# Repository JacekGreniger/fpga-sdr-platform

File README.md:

FPGA based SDR platform

Codec: AD9963
FPGA: Spartan 6 LX9, clock 48MHz
Host interface: USB 2.0, CY7C68013A in FIFO mode, clock 24MHz

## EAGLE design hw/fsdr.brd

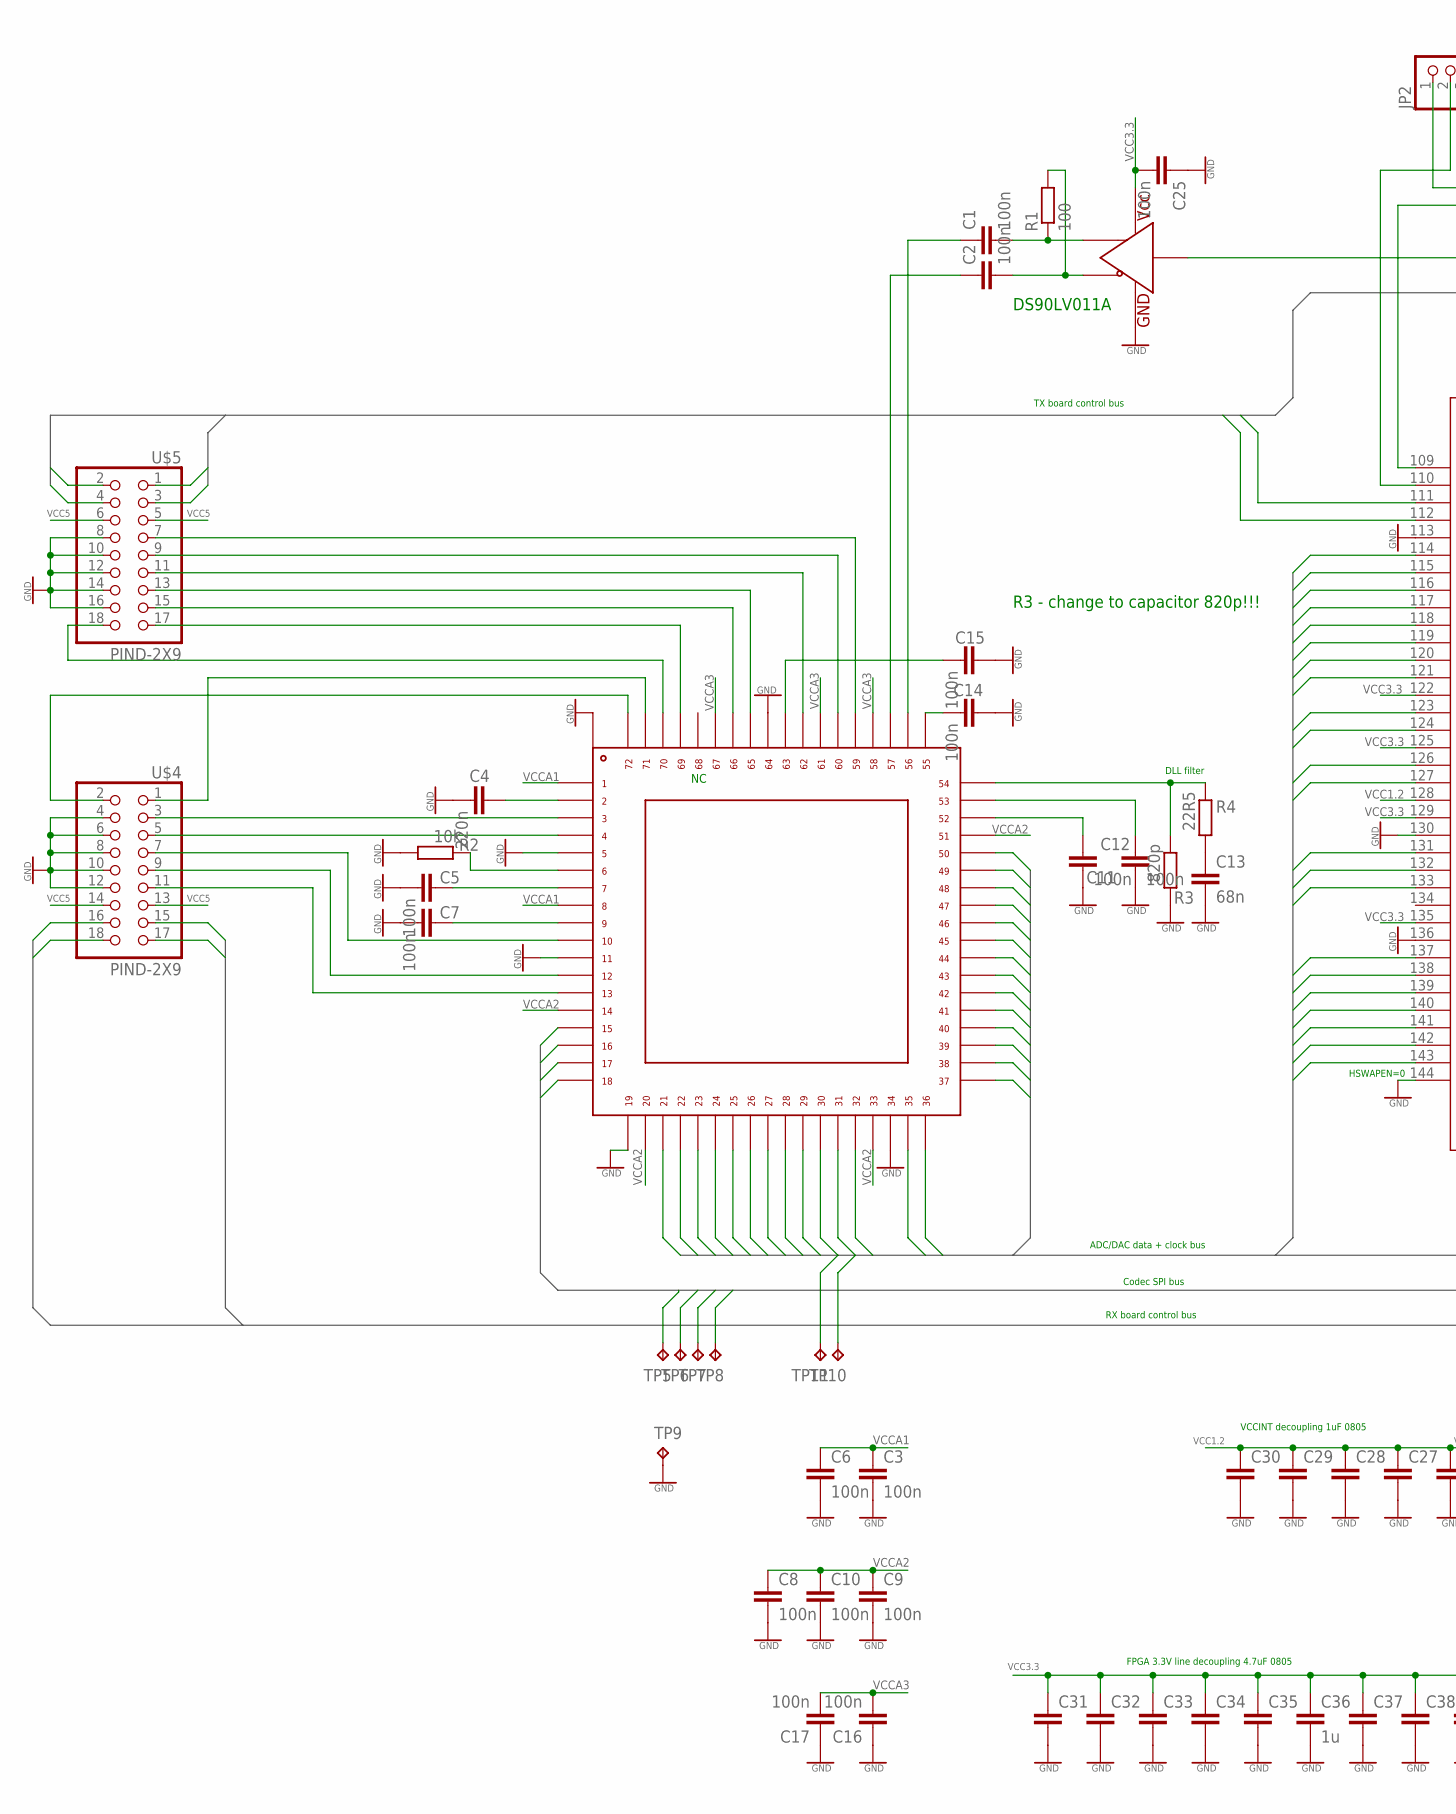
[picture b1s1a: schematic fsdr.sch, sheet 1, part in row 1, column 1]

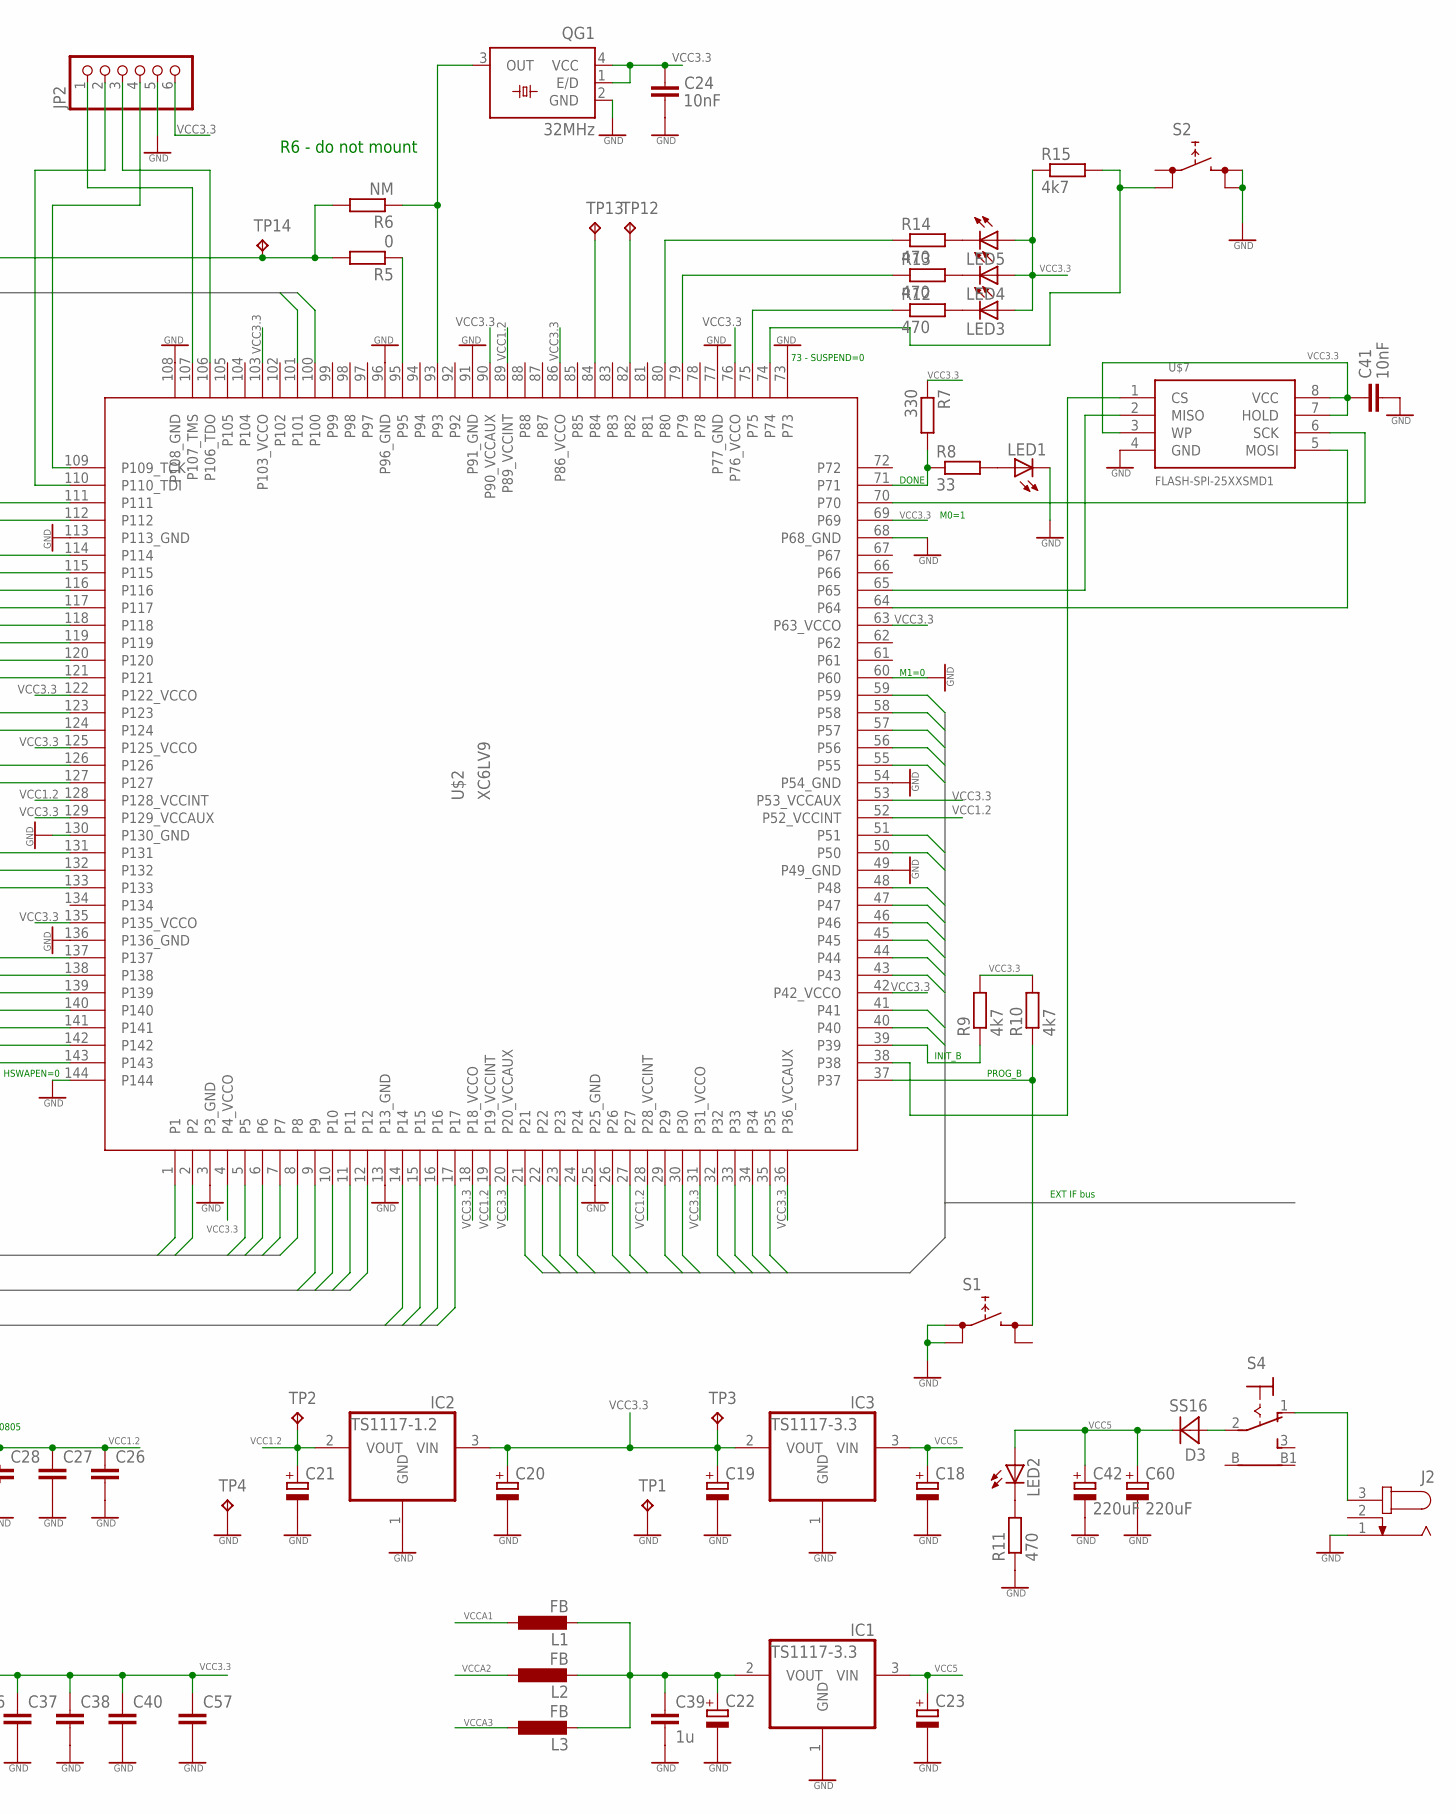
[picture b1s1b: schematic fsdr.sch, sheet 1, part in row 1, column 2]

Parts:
C1, C2, C3, C5, C6, C7, C8, C9, C10, C11, C12, C14, C15, C16, C17, C25: 100n; C0402
C4: 220n; C0402
C13: 68n; C0402
C18, C19, C20, C21, C22, C23: CPOL-EUSMCA; SMC_A
C24, C41: 10nF; C0402
C26, C27, C28, C29, C30, C31, C32, C33, C34, C35, C37, C38, C40, C57: C-EUC0805; C0805
C36, C39: 1u; C0805
C42, C60: 220uF; SMC_D
D3: SS16; SMA
IC1, IC3: TS1117-3.3; SOT223
IC2: TS1117-1.2; SOT223
J2: JACK-PLUG; SPC4078-NOSLOT
JP2: PINHD-1X6; 1X06
L1, L2, L3: FB; C0603
LED1, LED2, LED3, LED4, LED5: LEDSML0805; SML0805
QG1: 32MHz; SM77H
R1: 100; R0402
R2: 10k; R0402
R3: 820p; R0402
R4: 22R5; R0402
R5: 0; R0402
R6: NM; R0402
R7: 330; R0402
R8: 33; R0402
R9, R10, R15: 4k7; R0402
R11, R12, R13, R14: 470; R0402
S1, S2: SKHMPSE010; SKHMPXE010
S4: 9070-1W
TP1, TP2, TP3, TP4: TPPAD1-13; P1-13
TP5, TP6, TP7, TP8, TP9, TP10, TP11, TP12, TP13, TP14: TPB1,27; B1,27
U$1: AD9963; LFCSP72
U$2: XC6LV9; TQFP144
U$3: DS90LV011a; SOT23-5L
U$4, U$5: PIND-2X9; 2X9SMD
U$7: FLASH-SPI-25XXSMD1; SO08-EIAJ

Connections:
CS: TP7.TP, U$1.P$17, U$2.10
GND: C3.2, C4.2, C5.2, C6.2, C7.2, C8.2, C9.2, C10.2, C11.2, C12.2, C13.2, C14.1, C15.1, C16.1, C17.1, C18.-, C19.-, C20.-, C21.-, C22.-, C23.-, C24.1, C25.1, C26.2, C27.2, C28.2, C29.2, C30.2, C31.2, C32.2, C33.2, C34.2, C35.2, C36.2, C37.2, C38.2, C39.2, C40.2, C41.1, C42.-, C57.2, C60.-, IC1.1 (GND), IC2.1 (GND), IC3.1 (GND), J2.1, JP2.5, LED1.C, QG1.2 (GND), R2.2, R3.2, R11.1, S1.1 (1.1), S1.2 (1.2), S2.3 (2.1), S2.4 (2.2), TP1.TP, TP4.TP, TP9.TP, U$1.P$5, U$1.P$11, U$1.P$19, U$1.P$34, U$1.P$64, U$1.P$73_PAD, U$2.3 (P3_GND), U$2.13 (P13_GND), U$2.25 (P25_GND), U$2.49 (P49_GND), U$2.54 (P54_GND), U$2.60, U$2.68 (P68_GND), U$2.73, U$2.77 (P77_GND), U$2.91 (P91_GND), U$2.96 (P96_GND), U$2.108 (P108_GND), U$2.113 (P113_GND), U$2.130 (P130_GND), U$2.136 (P136_GND), U$2.144, U$3.2 (GND), U$4.4, U$4.6, U$4.8, U$4.10, U$4.12, U$5.8, U$5.10, U$5.12, U$5.14, U$5.16, U$7.4 (GND); also elsewhere on the board
unnamed: R7.2, R8.1, U$2.71
unnamed: QG1.3 (OUT), R6.1, U$2.93
unnamed: LED1.A, R8.2
unnamed: JP2.1, U$2.107 (P107_TMS)
unnamed: JP2.3, U$2.106 (P106_TDO)
unnamed: JP2.4, U$2.109 (P109_TCK)
unnamed: JP2.2, U$2.110 (P110_TDI)
unnamed: R10.1, S1.3 (2.1), U$2.37
unnamed: U$1.P$3, U$4.3
unnamed: U$1.P$4, U$4.5
unnamed: U$1.P$10, U$4.7
unnamed: U$1.P$12, U$4.9
unnamed: C7.1, U$1.P$9
unnamed: U$1.P$72, U$4.2
unnamed: U$1.P$71, U$4.1
unnamed: U$1.P$70, U$5.18
unnamed: U$1.P$69, U$5.17
unnamed: U$1.P$66, U$5.15
unnamed: U$1.P$65, U$5.13
unnamed: U$1.P$62, U$5.11
unnamed: U$1.P$60, U$5.9
unnamed: U$1.P$59, U$5.7
unnamed: C1.2, R1.1, U$3.4 (OUT)
unnamed: C2.2, R1.2, U$3.3 (/OUT)
unnamed: C2.1, U$1.P$57
unnamed: C13.1, R4.2
unnamed: C1.1, U$1.P$56
unnamed: R9.1, U$2.39
unnamed: U$1.P$13, U$4.11
unnamed: R2.1, U$1.P$6
unnamed: C5.1, U$1.P$7
unnamed: C4.1, U$1.P$2
unnamed: C14.2, U$1.P$55
unnamed: C15.2, U$1.P$63
unnamed: R3.1, R4.1, U$1.P$54
unnamed: C12.1, U$1.P$53
unnamed: C11.1, U$1.P$52
unnamed: R5.2, R6.2, TP14.TP, U$3.5 (IN)
unnamed: R5.1, U$2.95
unnamed: TP12.TP, U$2.82
unnamed: TP13.TP, U$2.84
unnamed: D3.A, S4.2
unnamed: LED2.C, R11.2
unnamed: C22.+, C39.1, IC1.2 (VOUT), L1.2, L2.2, L3.2
unnamed: J2.3, S4.1 (O)
unnamed: U$2.38, U$7.1 (CS)
unnamed: U$2.64, U$7.5 (MOSI)
unnamed: U$2.70, U$7.6 (SCK)
unnamed: U$2.65, U$7.2 (MISO)
unnamed: R12.1, U$2.75
unnamed: LED3.C, R12.2
unnamed: LED4.C, R13.2
unnamed: LED5.C, R14.2
unnamed: R13.1, U$2.79
unnamed: R14.1, U$2.80
unnamed: R15.2, S2.2 (1.2), U$2.74
P14: U$2.14, U$4.16
P15: U$2.15, U$4.15
P16: U$2.16, U$4.18
P17: U$2.17, U$4.17
P21: U$2.21; also elsewhere on the board
P22: U$2.22; also elsewhere on the board
P23: U$2.23; also elsewhere on the board
P24: U$2.24; also elsewhere on the board
P26: U$2.26; also elsewhere on the board
P27: U$2.27; also elsewhere on the board
P29: U$2.29; also elsewhere on the board
P30: U$2.30; also elsewhere on the board
P32: U$2.32; also elsewhere on the board
P33: U$2.33; also elsewhere on the board
P34: U$2.34; also elsewhere on the board
P35: U$2.35; also elsewhere on the board
P40: U$2.40; also elsewhere on the board
P41: U$2.41; also elsewhere on the board
P43: U$2.43; also elsewhere on the board
P44: U$2.44; also elsewhere on the board
P45: U$2.45; also elsewhere on the board
P46: U$2.46; also elsewhere on the board
P47: U$2.47; also elsewhere on the board
P48: U$2.48; also elsewhere on the board
P50: U$2.50; also elsewhere on the board
P51: U$2.51; also elsewhere on the board
P55: U$2.55; also elsewhere on the board
P56: U$2.56; also elsewhere on the board
P57: U$2.57; also elsewhere on the board
P58: U$2.58; also elsewhere on the board
P59: U$2.59; also elsewhere on the board
P61: U$2.61
P85: U$2.85
P88: U$2.88
P98: U$2.98
P100: U$2.100, U$5.2
P101: U$2.101, U$5.1
P111: U$2.111, U$5.4
P112: U$2.112, U$5.3
RES: TP5.TP, U$1.P$15, U$2.12
SCK: TP6.TP, U$1.P$16, U$2.11
SD: TP8.TP, U$1.P$18, U$2.9
TRXCLK: TP11.TP, U$1.P$36, U$2.133
TRXD0: U$1.P$32, U$2.138
TRXD1: U$1.P$31, U$2.139
TRXD2: U$1.P$30, U$2.140
TRXD3: U$1.P$29, U$2.141
TRXD4: U$1.P$28, U$2.142
TRXD5: U$1.P$27, U$2.143
TRXD6: U$1.P$26, U$2.1
TRXD7: U$1.P$25, U$2.2
TRXD8: U$1.P$24, U$2.5
TRXD9: U$1.P$23, U$2.6
TRXD10: U$1.P$22, U$2.7
TRXD11: U$1.P$21, U$2.8
TRXIQ: U$1.P$35, U$2.137
TXCLK: TP10.TP, U$1.P$37, U$2.132
TXD0: U$1.P$50, U$2.114
TXD1: U$1.P$49, U$2.115
TXD2: U$1.P$48, U$2.116
TXD3: U$1.P$47, U$2.117
TXD4: U$1.P$46, U$2.118
TXD5: U$1.P$45, U$2.119
TXD6: U$1.P$44, U$2.120
TXD7: U$1.P$43, U$2.121
TXD8: U$1.P$42, U$2.123
TXD9: U$1.P$41, U$2.124
TXD10: U$1.P$40, U$2.126
TXD11: U$1.P$39, U$2.127
TXIQ: U$1.P$38, U$2.131
VCC1.2: C21.+, C26.1, C27.1, C28.1, C29.1, C30.1, IC2.2 (VOUT), TP2.TP, U$2.19 (P19_VCCINT), U$2.28 (P28_VCCINT), U$2.52 (P52_VCCINT), U$2.89 (P89_VCCINT), U$2.128 (P128_VCCINT)
VCC3.3: C19.+, C20.+, C24.2, C25.2, C31.1, C32.1, C33.1, C34.1, C35.1, C36.1, C37.1, C38.1, C40.1, C41.2, C57.1, IC2.3 (VIN), IC3.2 (VOUT), JP2.6, LED3.A, LED4.A, LED5.A, QG1.1 (E/D), QG1.4 (VCC), R7.1, R9.2, R10.2, R15.1, TP3.TP, U$2.4 (P4_VCCO), U$2.18 (P18_VCCO), U$2.20 (P20_VCCAUX), U$2.31 (P31_VCCO), U$2.36 (P36_VCCAUX), U$2.42 (P42_VCCO), U$2.53 (P53_VCCAUX), U$2.63 (P63_VCCO), U$2.69, U$2.76 (P76_VCCO), U$2.86 (P86_VCCO), U$2.90 (P90_VCCAUX), U$2.103 (P103_VCCO), U$2.122 (P122_VCCO), U$2.125 (P125_VCCO), U$2.129 (P129_VCCAUX), U$2.135 (P135_VCCO), U$3.1 (VCC), U$7.3 (WP), U$7.7 (HOLD), U$7.8 (VCC)
VCC5: C18.+, C23.+, C42.+, C60.+, D3.C, IC1.3 (VIN), IC3.3 (VIN), LED2.A, U$4.13, U$4.14, U$5.5, U$5.6; also elsewhere on the board
VCCA1: C3.1, C6.1, L1.1, U$1.P$1, U$1.P$8
VCCA2: C8.1, C9.1, C10.1, L2.1, U$1.P$14, U$1.P$20, U$1.P$33, U$1.P$51
VCCA3: C16.2, C17.2, L3.1, U$1.P$58, U$1.P$61, U$1.P$67

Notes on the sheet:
VCCINT decoupling 1uF 0805
HSWAPEN=0
73 - SUSPEND=0
DONE
M1=0
M0=1
PROG_B
INIT_B
FPGA 3.3V line decoupling 4.7uF 0805
Codec SPI bus
RX board control bus
ADC/DAC data + clock bus
DLL filter
TX board control bus
EXT IF bus
R3 - change to capacitor 820p!!!
R6 - do not mount
DS90LV011A

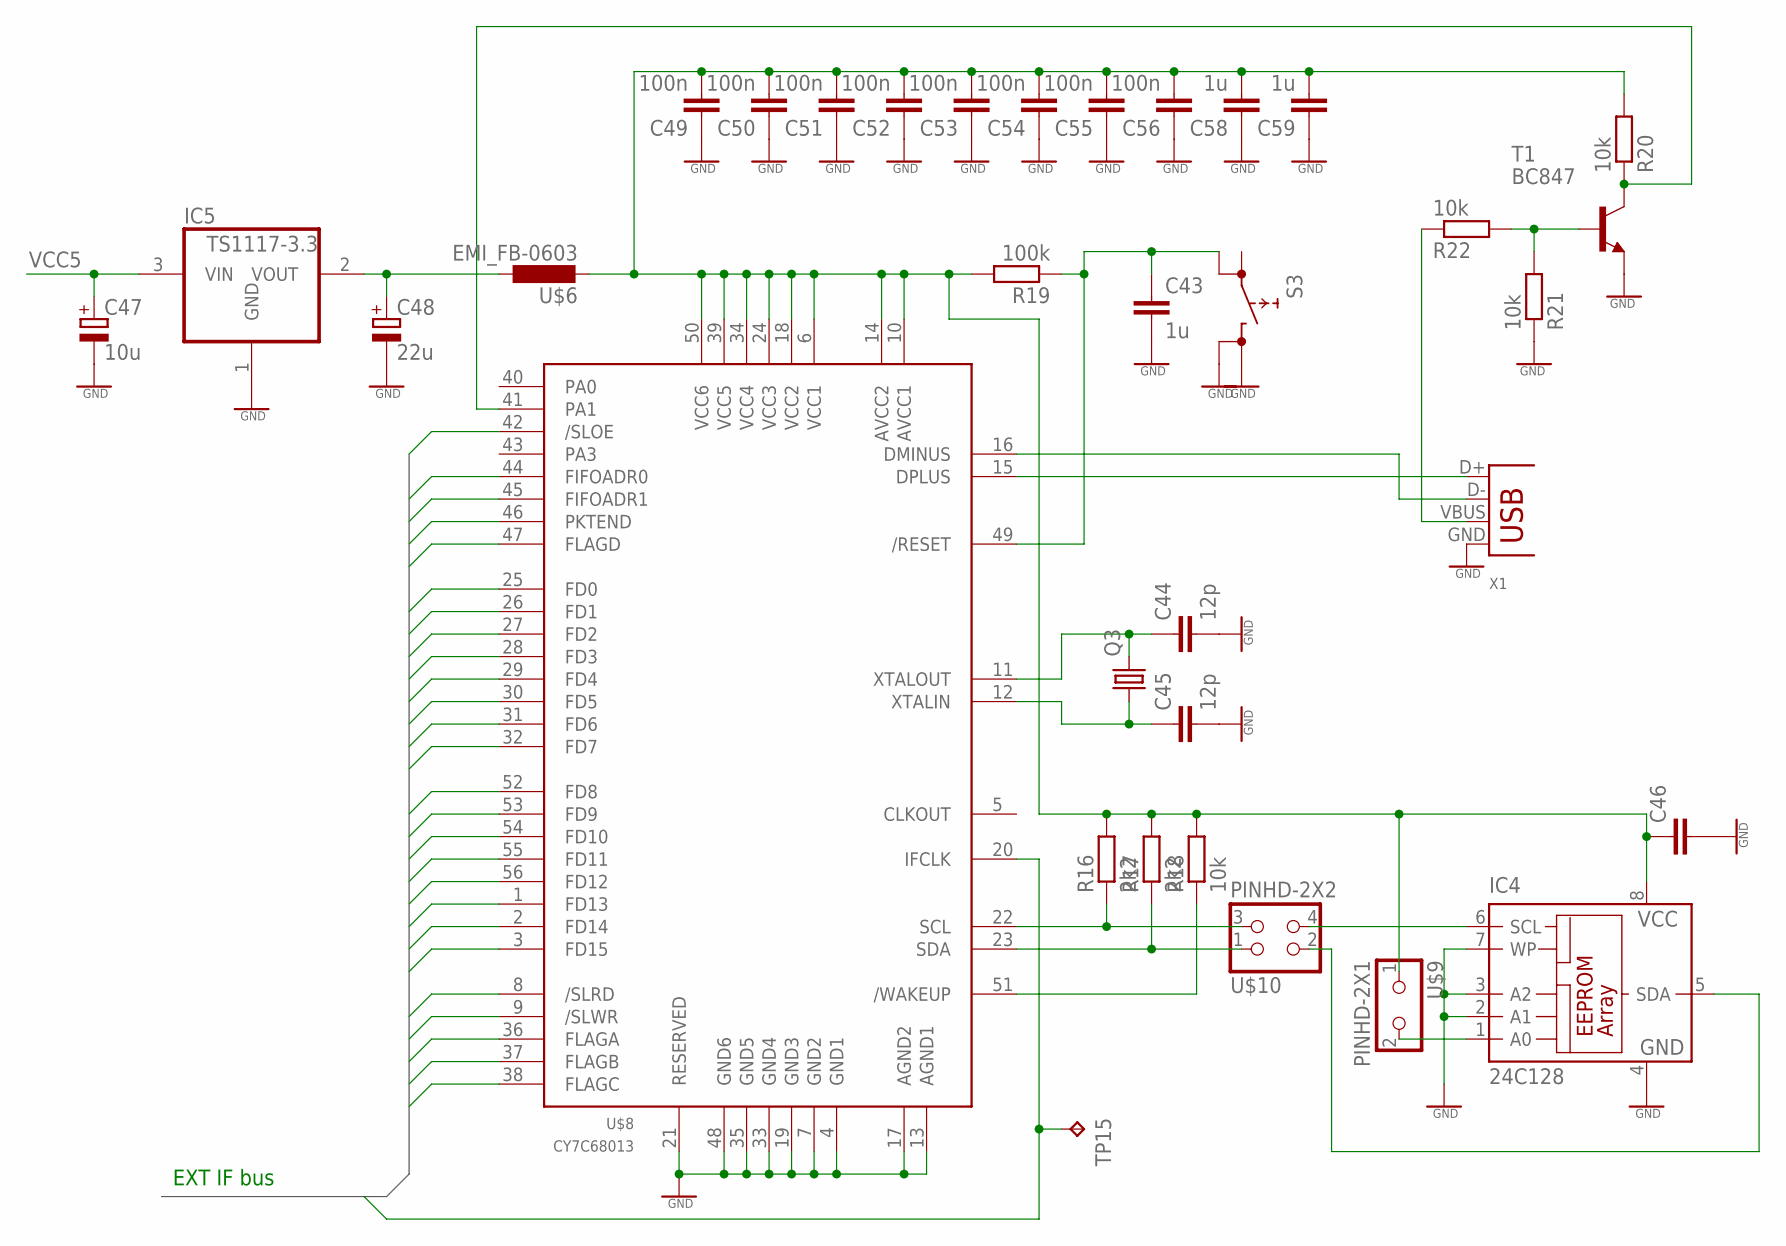
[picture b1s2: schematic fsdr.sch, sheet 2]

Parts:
C43, C58, C59: 1u; C0402
C44, C45: 12p; C0402
C46: C-EUC0402; C0402
C47: 10u; SMC_A
C48: 22u; SMC_A
C49, C50, C51, C52, C53, C54, C55, C56: 100n; C0402
IC4: 24C128; SO-08
IC5: TS1117-3.3; SOT223
Q3: CRYSTALHC49U-V; HC49U-V
R16, R17: 2k2; R0402
R18, R20, R21, R22: 10k; R0402
R19: 100k; R0402
S3: SKHMPSE010; SKHMPXE010
T1: BC847; SOT23
TP15: TPB1,27; B1,27
U$6: EMI_FB-0603; C0603
U$8: CY7C68013; 56-SSOP
U$9: PINHD-2X1; 2X1SMD
U$10: PINHD-2X2; 2X2SMD
X1: USB-MB-S

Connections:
GND: C43.2, C44.2, C45.2, C46.2, C47.-, C48.-, C49.1, C50.1, C51.1, C52.1, C53.1, C54.1, C55.1, C56.1, C58.1, C59.1, IC4.2 (A1), IC4.3 (A2), IC4.4 (GND), IC4.7 (WP), IC5.1 (GND), R21.1, S3.3 (2.1), S3.4 (2.2), T1.2 (E), U$8.4 (GND1), U$8.7 (GND2), U$8.13 (AGND1), U$8.17 (AGND2), U$8.19 (GND3), U$8.21 (RESERVED), U$8.33 (GND4), U$8.35 (GND5), U$8.48 (GND6), X1.GND; also elsewhere on the board
unnamed: U$8.15 (DPLUS), X1.D+
unnamed: U$8.16 (DMINUS), X1.D-
unnamed: C43.1, R19.1, S3.2 (1.2), U$8.49 (/RESET)
unnamed: R16.1, U$8.22 (SCL), U$10.3
unnamed: IC4.5 (SDA), U$10.2
unnamed: R18.1, U$8.51 (/WAKEUP)
unnamed: C44.1, Q3.2, U$8.11 (XTALOUT)
unnamed: C45.1, Q3.1, U$8.12 (XTALIN)
unnamed: C46.1, C49.2, C50.2, C51.2, C52.2, C53.2, C54.2, C55.2, C56.2, C58.2, C59.2, IC4.8 (VCC), R16.2, R17.2, R18.2, R19.2, R20.2, U$6.2, U$8.6 (VCC1), U$8.10 (AVCC1), U$8.14 (AVCC2), U$8.18 (VCC2), U$8.24 (VCC3), U$8.34 (VCC4), U$8.39 (VCC5), U$8.50 (VCC6), U$9.1
unnamed: IC4.1 (A0), U$9.2
unnamed: C48.+, IC5.2 (VOUT), U$6.1
unnamed: R22.1, X1.VBUS
unnamed: R17.1, U$8.23 (SDA), U$10.1
unnamed: IC4.6 (SCL), U$10.4
unnamed: R20.1, T1.3 (C), U$8.41 (PA1)
unnamed: R21.2, R22.2, T1.1 (B)
P21: U$8.56 (FD12); also elsewhere on the board
P22: U$8.55 (FD11); also elsewhere on the board
P23: U$8.54 (FD10); also elsewhere on the board
P24: U$8.53 (FD9); also elsewhere on the board
P26: U$8.52 (FD8); also elsewhere on the board
P27: U$8.47 (FLAGD); also elsewhere on the board
P29: U$8.46 (PKTEND); also elsewhere on the board
P30: U$8.45 (FIFOADR1); also elsewhere on the board
P32: U$8.44 (FIFOADR0); also elsewhere on the board
P33: U$8.42 (/SLOE); also elsewhere on the board
P34: U$8.38 (FLAGC); also elsewhere on the board
P35: U$8.37 (FLAGB); also elsewhere on the board
P40: U$8.29 (FD4); also elsewhere on the board
P41: U$8.30 (FD5); also elsewhere on the board
P43: U$8.31 (FD6); also elsewhere on the board
P44: U$8.32 (FD7); also elsewhere on the board
P45: U$8.36 (FLAGA); also elsewhere on the board
P46: U$8.27 (FD2); also elsewhere on the board
P47: U$8.28 (FD3); also elsewhere on the board
P48: U$8.26 (FD1); also elsewhere on the board
P50: U$8.25 (FD0); also elsewhere on the board
P51: TP15.TP, U$8.20 (IFCLK); also elsewhere on the board
P55: U$8.9 (/SLWR); also elsewhere on the board
P56: U$8.8 (/SLRD); also elsewhere on the board
P57: U$8.3 (FD15); also elsewhere on the board
P58: U$8.2 (FD14); also elsewhere on the board
P59: U$8.1 (FD13); also elsewhere on the board
VCC5: C47.+, IC5.3 (VIN); also elsewhere on the board

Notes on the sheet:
EXT IF bus

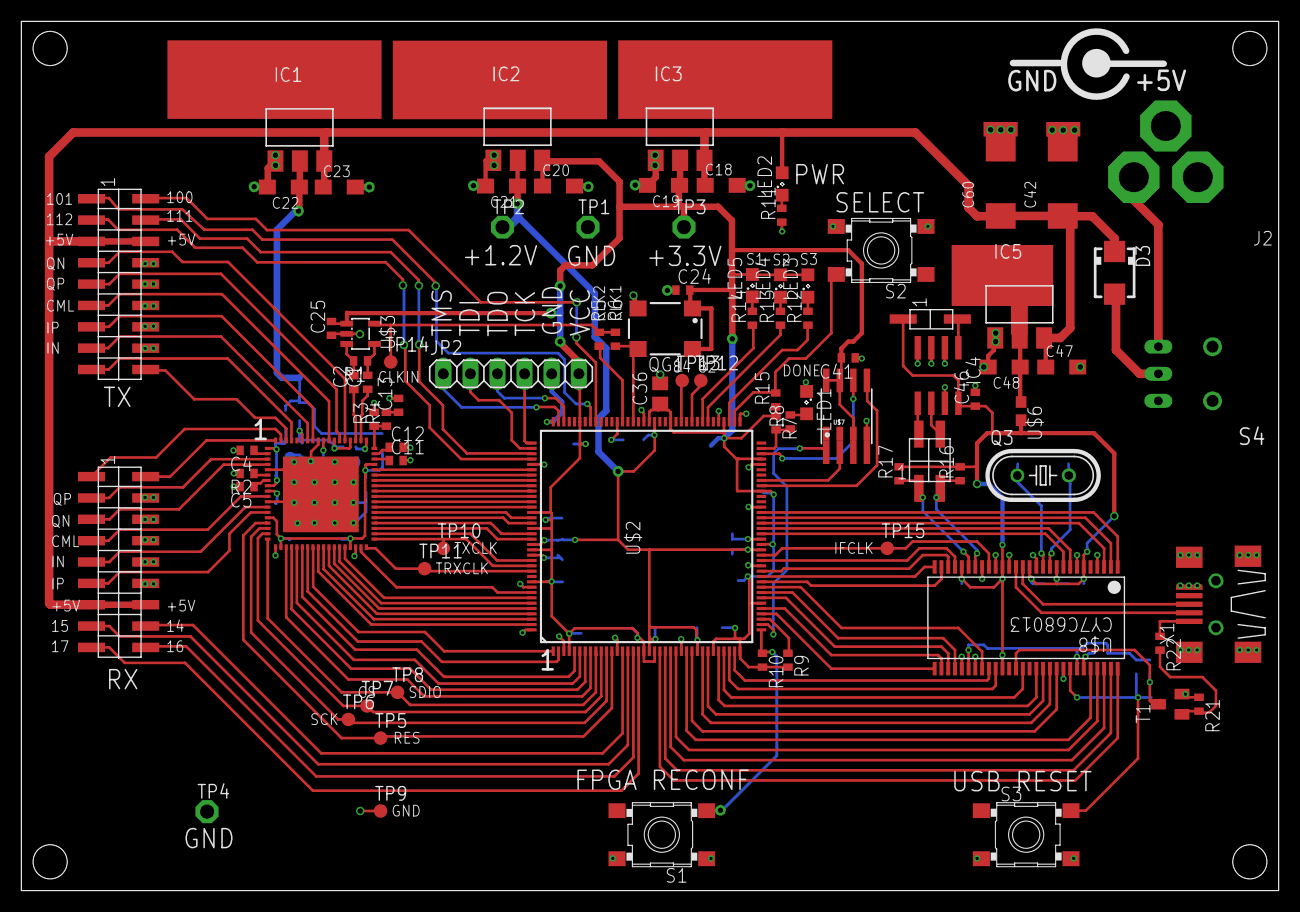
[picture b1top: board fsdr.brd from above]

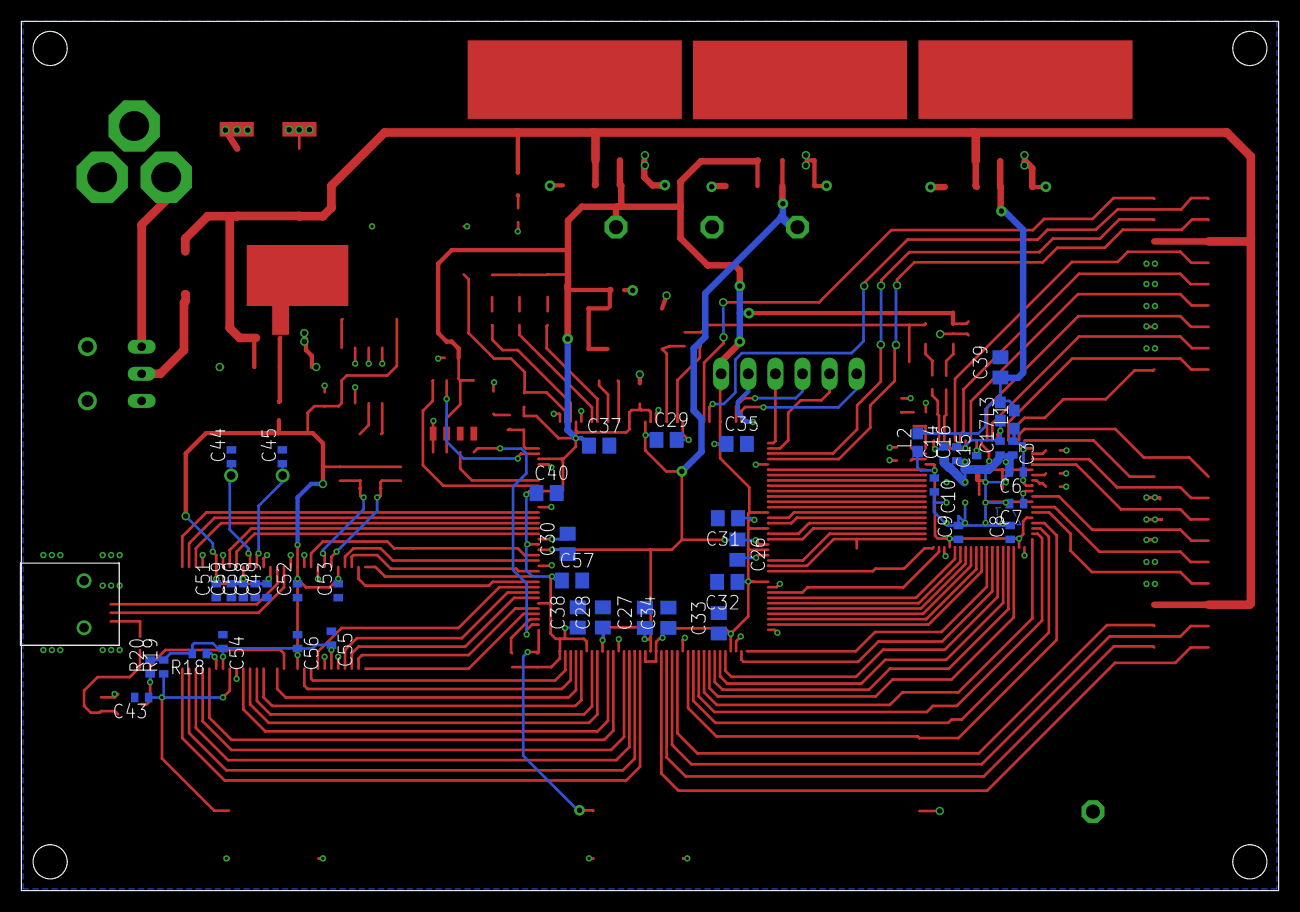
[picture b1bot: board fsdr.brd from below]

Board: 2 copper layers, 117.8 x 81.4 mm, 131 parts (44 on the bottom side), 146 nets.

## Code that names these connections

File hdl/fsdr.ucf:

#UCF for Xilinx Spartan 6
#23.12.2012

NET	CLK_IN	LOC="P93"	  | IOSTANDARD=LVTTL;
#NET "CLK_IN" CLOCK_DEDICATED_ROUTE = FALSE;
NET	CODEC_CLK_OUT	LOC="P95"	  | IOSTANDARD=LVTTL | slew=FAST;

NET	BUTTON_SELECT	LOC="P74"	  | IOSTANDARD=LVTTL;

NET	LED_S1	LOC="P80"	  | IOSTANDARD=LVTTL;
NET	LED_S2	LOC="P79"	  | IOSTANDARD=LVTTL;
NET	LED_S3	LOC="P75"	  | IOSTANDARD=LVTTL;

NET	TP82	  LOC="P82"	  | IOSTANDARD=LVTTL;
NET	TP84	  LOC="P84"	  | IOSTANDARD=LVTTL;


NET	FD(0)	        LOC="P50"	  | IOSTANDARD=LVTTL | slew=FAST;
NET	FD(1)	        LOC="P48"	  | IOSTANDARD=LVTTL | slew=FAST;
NET	FD(2)	        LOC="P46"	  | IOSTANDARD=LVTTL | slew=FAST;
NET	FD(3)	        LOC="P47"	  | IOSTANDARD=LVTTL | slew=FAST;
NET	FD(4)	        LOC="P40"	  | IOSTANDARD=LVTTL | slew=FAST;
NET	FD(5)	        LOC="P41"	  | IOSTANDARD=LVTTL | slew=FAST;
NET	FD(6)	        LOC="P43"	  | IOSTANDARD=LVTTL | slew=FAST;
NET	FD(7)	        LOC="P44"	  | IOSTANDARD=LVTTL | slew=FAST;
NET	FD(8)	        LOC="P26"	  | IOSTANDARD=LVTTL | slew=FAST;
NET	FD(9)	        LOC="P24"	  | IOSTANDARD=LVTTL | slew=FAST;
NET	FD(10)	      LOC="P23"	  | IOSTANDARD=LVTTL | slew=FAST;
NET	FD(11)	      LOC="P22"	  | IOSTANDARD=LVTTL | slew=FAST;
NET	FD(12)	      LOC="P21"	  | IOSTANDARD=LVTTL | slew=FAST;
NET	FD(13)	      LOC="P59"	  | IOSTANDARD=LVTTL | slew=FAST;
NET	FD(14)	      LOC="P58"	  | IOSTANDARD=LVTTL | slew=FAST;
NET	FD(15)	      LOC="P57"	  | IOSTANDARD=LVTTL | slew=FAST;

NET	FLAGA	        LOC="P45"	  | IOSTANDARD=LVTTL;
NET	FLAGB	        LOC="P35"	  | IOSTANDARD=LVTTL;
NET	FLAGC	        LOC="P34"	  | IOSTANDARD=LVTTL;
NET	FLAGD	        LOC="P27"	  | IOSTANDARD=LVTTL;

NET	PKTEND	     LOC="P29"	  | IOSTANDARD=LVTTL | slew=FAST;
NET	FIFOADR(1)	  LOC="P30"	  | IOSTANDARD=LVTTL | slew=FAST;
NET	FIFOADR(0)	  LOC="P32"	  | IOSTANDARD=LVTTL | slew=FAST;
NET	SLOE	        LOC="P33"	  | IOSTANDARD=LVTTL | slew=FAST;			
NET	SLWR	        LOC="P55"	  | IOSTANDARD=LVTTL | slew=FAST;
NET	SLRD	        LOC="P56"	  | IOSTANDARD=LVTTL | slew=FAST;

NET	IFCLK	        LOC="P51"	  | IOSTANDARD=LVTTL | slew=FAST;


NET	TXD(0)	LOC="P114"	  | IOSTANDARD=LVTTL | slew=FAST;
NET	TXD(1)	LOC="P115"	  | IOSTANDARD=LVTTL | slew=FAST;
NET	TXD(2)	LOC="P116"	  | IOSTANDARD=LVTTL | slew=FAST;
NET	TXD(3)	LOC="P117"	  | IOSTANDARD=LVTTL | slew=FAST;
NET	TXD(4)	LOC="P118"	  | IOSTANDARD=LVTTL | slew=FAST;
NET	TXD(5)	LOC="P119"	  | IOSTANDARD=LVTTL | slew=FAST;
NET	TXD(6)	LOC="P120"	  | IOSTANDARD=LVTTL | slew=FAST;
NET	TXD(7)	LOC="P121"	  | IOSTANDARD=LVTTL | slew=FAST;
NET	TXD(8)	LOC="P123"	  | IOSTANDARD=LVTTL | slew=FAST;
NET	TXD(9)	LOC="P124"	  | IOSTANDARD=LVTTL | slew=FAST;
NET	TXD(10)	LOC="P126"	  | IOSTANDARD=LVTTL | slew=FAST;
NET	TXD(11)	LOC="P127"	  | IOSTANDARD=LVTTL | slew=FAST;

NET	TXIQ	  LOC="P131"	  | IOSTANDARD=LVTTL | slew=FAST;
NET	TXCLK	  LOC="P132"	  | IOSTANDARD=LVTTL | slew=FAST;

NET	TX_SCLK	LOC="P100"	  | IOSTANDARD=LVTTL;		
NET	TX_SCS	LOC="P101"	  | IOSTANDARD=LVTTL;
NET	TX_SDAT	LOC="P111"	  | IOSTANDARD=LVTTL;
NET	TX_AUX	LOC="P112"	  | IOSTANDARD=LVTTL;


NET	TRXD(0)	 LOC="P138"	| IOSTANDARD=LVTTL | slew=FAST;
NET	TRXD(1)	 LOC="P139"	| IOSTANDARD=LVTTL | slew=FAST;
NET	TRXD(2)	 LOC="P140"	| IOSTANDARD=LVTTL | slew=FAST;
NET	TRXD(3)	 LOC="P141"	| IOSTANDARD=LVTTL | slew=FAST;
NET	TRXD(4)	 LOC="P142"	| IOSTANDARD=LVTTL | slew=FAST;
NET	TRXD(5)	 LOC="P143"	| IOSTANDARD=LVTTL | slew=FAST;
NET	TRXD(6)	 LOC="P1"	  | IOSTANDARD=LVTTL | slew=FAST;
NET	TRXD(7)   LOC="P2"	  | IOSTANDARD=LVTTL | slew=FAST;
NET	TRXD(8)	 LOC="P5"	  | IOSTANDARD=LVTTL | slew=FAST;
NET	TRXD(9)	 LOC="P6"	  | IOSTANDARD=LVTTL | slew=FAST;
NET	TRXD(10)  LOC="P7"	  | IOSTANDARD=LVTTL | slew=FAST;
NET	TRXD(11)  LOC="P8"	  | IOSTANDARD=LVTTL | slew=FAST;				

NET	TRXIQ	    LOC="P137"	  | IOSTANDARD=LVTTL | slew=FAST;
NET	TRXCLK    LOC="P133"	  | IOSTANDARD=LVTTL | slew=FAST;

NET	RX_SCS	LOC="P14"	  | IOSTANDARD=LVTTL;
NET	RX_SCLK	LOC="P15"	  | IOSTANDARD=LVTTL;
NET	RX_SDAT	LOC="P16"	  | IOSTANDARD=LVTTL;
NET	RX_AUX 	LOC="P17"	  | IOSTANDARD=LVTTL;


NET	CODEC_SDAT	  LOC="P9"	  | IOSTANDARD=LVTTL;
NET	CODEC_SCS     LOC="P10"	  | IOSTANDARD=LVTTL;
NET	CODEC_SCLK	  LOC="P11"	  | IOSTANDARD=LVTTL;
NET	CODEC_RESET	  LOC="P12"	  | IOSTANDARD=LVTTL;


#NET FLASH_CS LOC="P38"  | IOSTANDARD=LVTTL | DRIVE=8 | SLEW=FAST;          # FLASH_CS
#NET FLASH_CK LOC="P70"  | IOSTANDARD=LVTTL | DRIVE=8 | SLEW=FAST;          # FLASH_CK
#NET FLASH_SI LOC="P64"  | IOSTANDARD=LVTTL | DRIVE=8 | SLEW=FAST;          # FLASH_SI
#NET FLASH_SO LOC="P65"  | IOSTANDARD=LVTTL | DRIVE=8 | SLEW=FAST | PULLUP; # FLASH_SO

#NET JTAG_TMS LOC="P107" | IOSTANDARD=LVTTL | DRIVE=8 | SLEW=FAST;          # JTAG_TMS
#NET JTAG_TCK LOC="P109" | IOSTANDARD=LVTTL | DRIVE=8 | SLEW=FAST;          # JTAG_TCK
#NET JTAG_TDI LOC="P110" | IOSTANDARD=LVTTL | DRIVE=8 | SLEW=FAST;          # JTAG_TDI
#NET JTAG_TDO LOC="P106" | IOSTANDARD=LVTTL | DRIVE=8 | SLEW=FAST;          # JTAG_TDO
